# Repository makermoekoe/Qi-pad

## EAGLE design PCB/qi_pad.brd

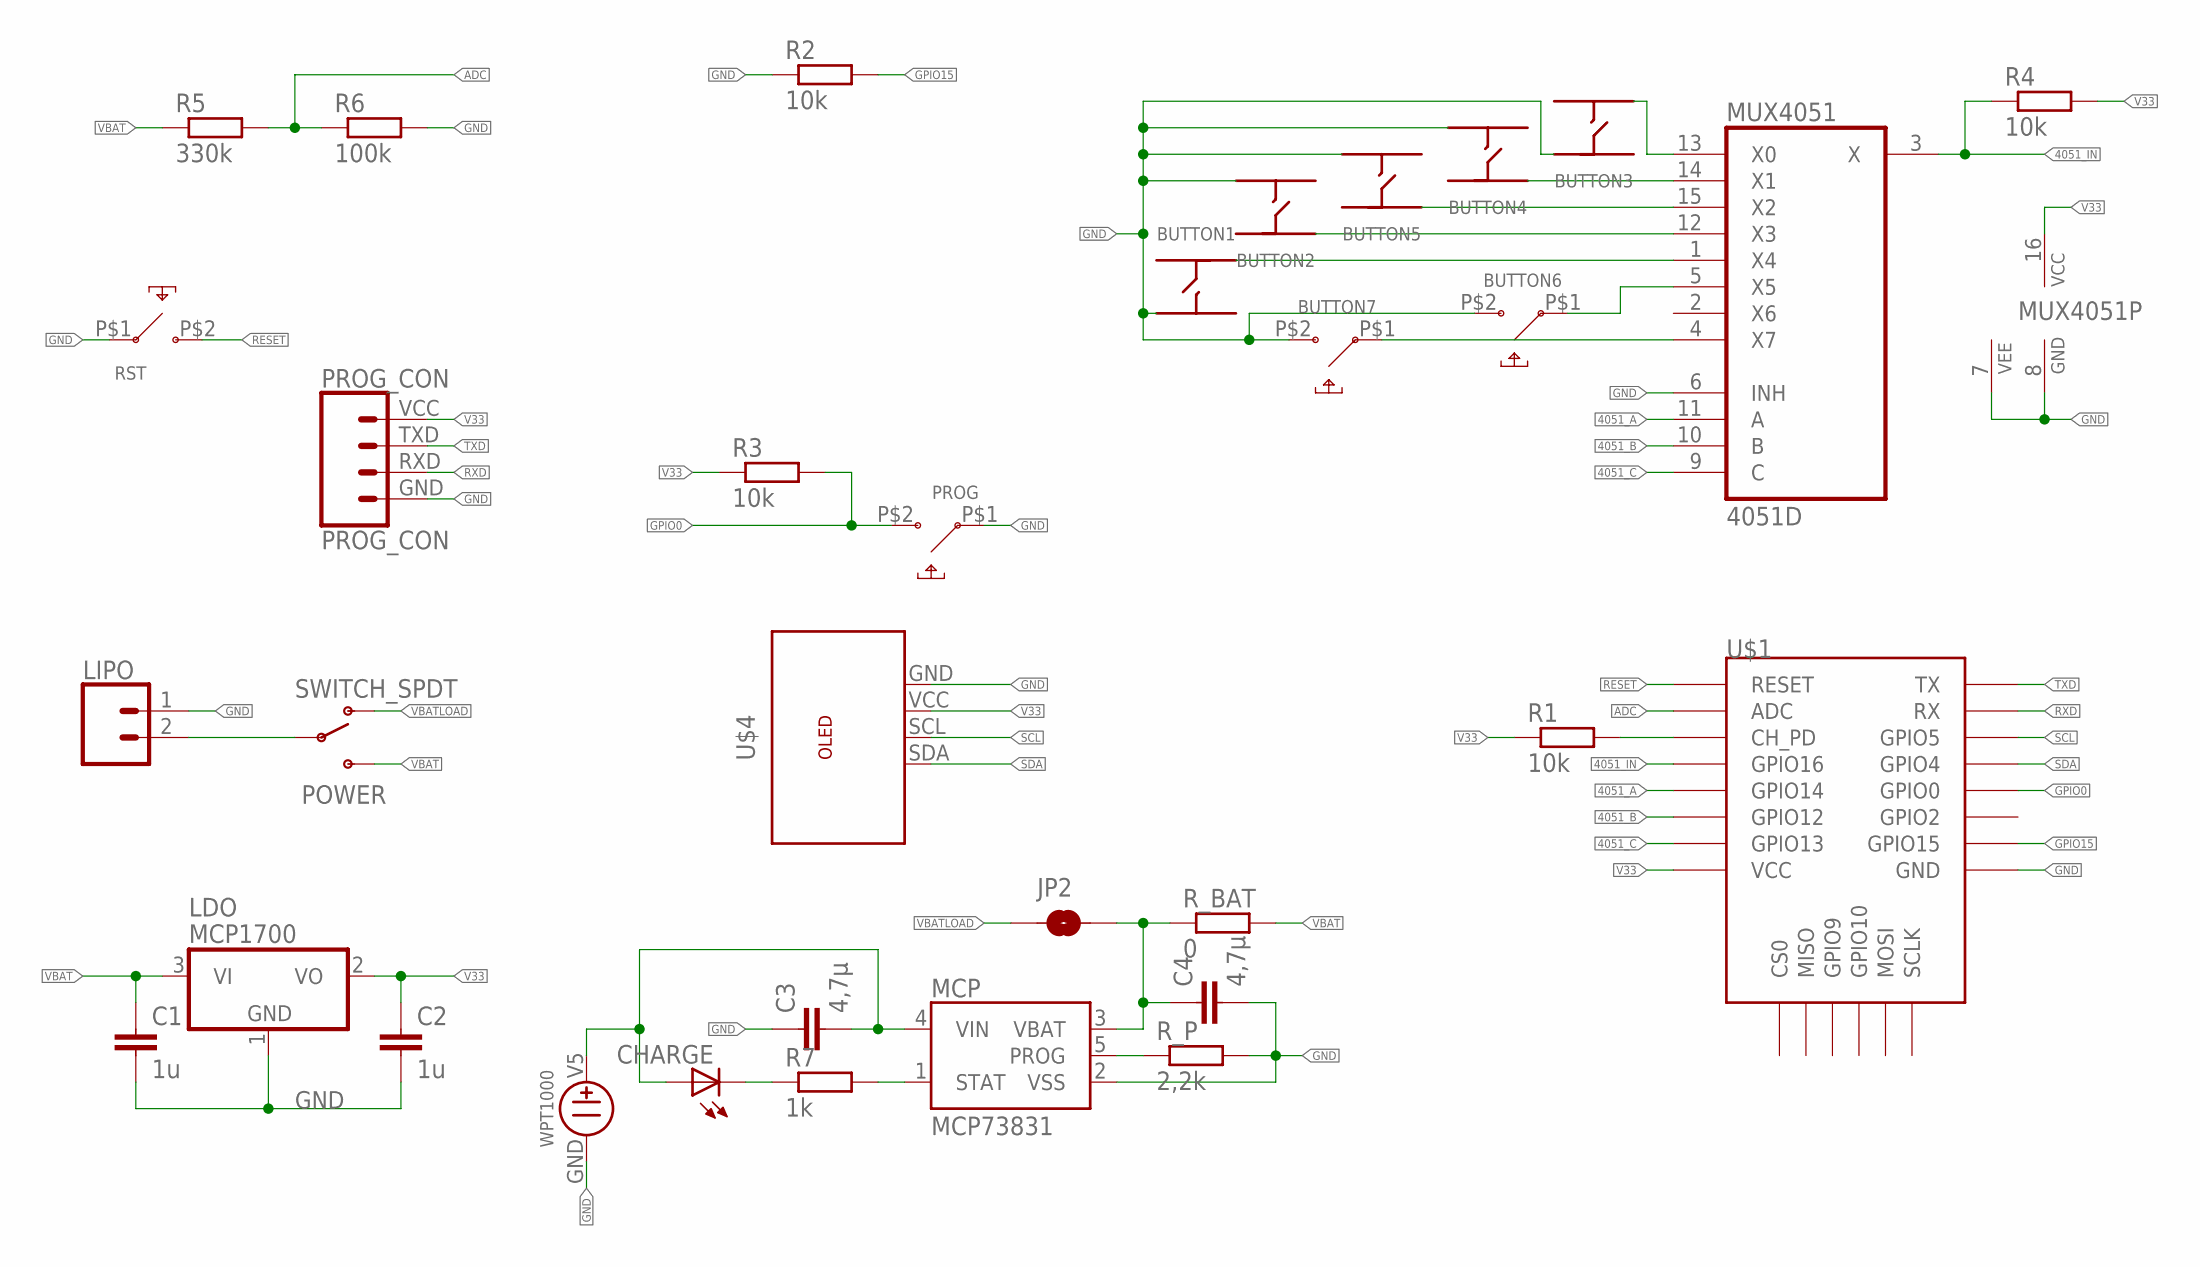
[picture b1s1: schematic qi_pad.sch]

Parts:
BUTTON1, BUTTON2, BUTTON3, BUTTON4, BUTTON5: 6X6BUTTON
BUTTON6, BUTTON7: 3X4_SMD_BUTTON; 3X4BUTTON
C1, C2: 1u; C1206
C3, C4: 4,7µ; C1206
CHARGE: LEDCHIPLED_1206; CHIPLED_1206
JP2: JUMPER-SMT_2_NO_NO-SILK; SMT-JUMPER_2_NO_NO-SILK
LDO: MCP1700; SOT23
LIPO: CONN_02-JST-2MM-SMT; JST-2-SMD
MCP: MCP73831; SOT23-5
MUX4051: 4051D; SO16
POWER: SWITCH_SPDT; KPS-1290
PROG: 3X6X3,5BUTTON90
PROG_CON: PROG_CON
R1, R2, R3, R4: 10k; R0603
R5: 330k; R0603
R6: 100k; R0603
R7: 1k; R0603
RST: 3X6X3,5BUTTON90
R_BAT: 0; R1206
R_P: 2,2k; R0603
U$1: ESP8266-12F-SMD; ESP8266-12F
U$4: OLED128X64; OLED_128X64
WPM1000: WPT1000

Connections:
4051_A: MUX4051.11 (A), U$1.GPIO14
4051_B: MUX4051.10 (B), U$1.GPIO12
4051_C: MUX4051.9 (C), U$1.GPIO13
4051_IN: MUX4051.3 (X), R4.1, U$1.GPIO16
ADC: R5.2, R6.1, U$1.ADC
GND: BUTTON1.P1 (A1), BUTTON2.P2 (A2), BUTTON3.P4 (U2), BUTTON4.P2 (A2), BUTTON5.P2 (A2), BUTTON6.P$2 (P2), BUTTON7.P$2 (P2), C1.2, C2.2, C3.1, C4.2, LDO.1 (GND), LIPO.1 (2), MCP.2 (VSS), MUX4051.6 (INH), MUX4051.7 (VEE), MUX4051.8 (GND), PROG.P$1 (P1), PROG_CON.GND (1), R2.1, R6.2, RST.P$1 (P1), R_P.2, U$1.GND, U$4.GND, WPM1000.GND
GPIO0: PROG.P$2 (P2), R3.2, U$1.GPIO0
GPIO15: R2.2, U$1.GPIO15
unnamed: BUTTON3.P1 (A1), MUX4051.13 (X0)
unnamed: LIPO.2 (1), POWER.P
unnamed: BUTTON6.P$1 (P1), MUX4051.5 (X5)
unnamed: MCP.1 (STAT), R7.2
unnamed: R1.2, U$1.EN (CH_PD)
unnamed: BUTTON7.P$1 (P1), MUX4051.4 (X7)
unnamed: BUTTON1.P4 (U2), MUX4051.1 (X4)
unnamed: MCP.5 (PROG), R_P.1
unnamed: BUTTON2.P3 (U1), MUX4051.12 (X3)
unnamed: CHARGE.C, R7.1
unnamed: BUTTON5.P3 (U1), MUX4051.15 (X2)
unnamed: BUTTON4.P3 (U1), MUX4051.14 (X1)
unnamed: C4.1, JP2.2, MCP.3 (VBAT), R_BAT.1
RESET: RST.P$2 (P2), U$1.RESET
RXD: PROG_CON.RXD (2), U$1.RXD (RX)
SCL: U$1.GPIO5, U$4.SCL
SDA: U$1.GPIO4, U$4.SDA
TXD: PROG_CON.TXD (3), U$1.TXD (TX)
V5: C3.2, CHARGE.A, MCP.4 (VIN), WPM1000.V5
V33: C2.1, LDO.2 (VO), MUX4051.16 (VCC), PROG_CON.VCC (4), R1.1, R3.1, R4.2, U$1.VCC, U$4.VCC
VBAT: C1.1, LDO.3 (VI), POWER.S, R5.1, R_BAT.2
VBATLOAD: JP2.1, POWER.O

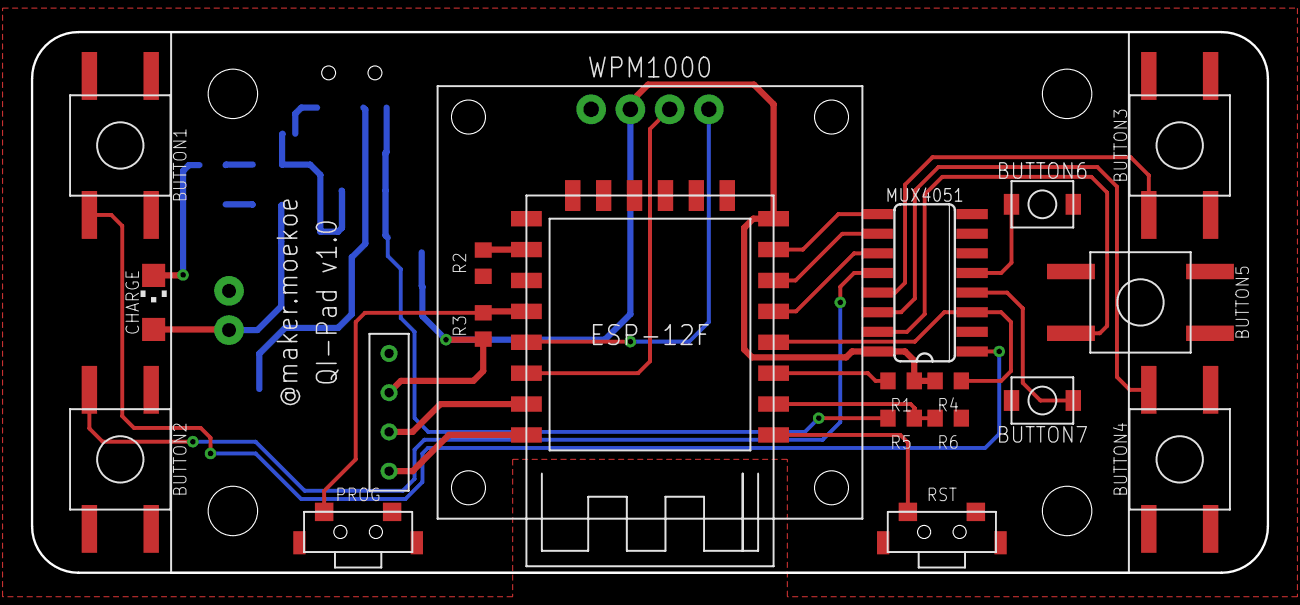
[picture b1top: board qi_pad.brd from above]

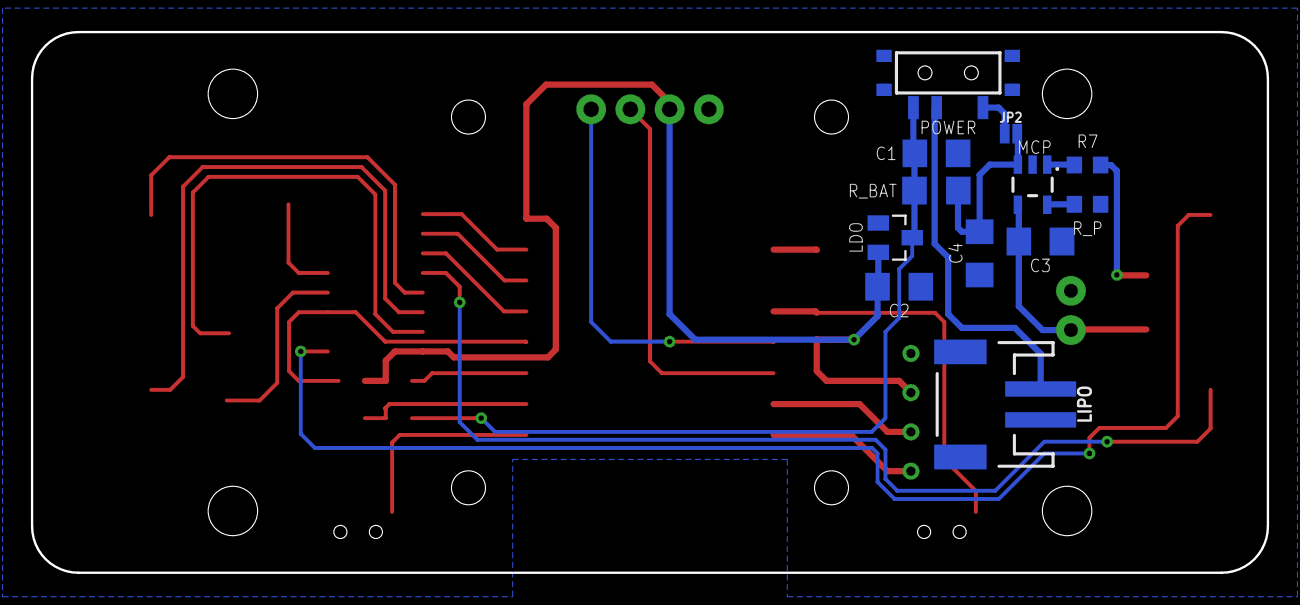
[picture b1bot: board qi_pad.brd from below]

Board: 2 copper layers, 80.0 x 35.0 mm, 33 parts (12 on the bottom side), 30 nets.

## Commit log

2019-02-10 basic idea
2019-02-10 added description and pictures
2019-05-22 added some videos
2019-05-22 added 3d printing case
2019-05-22 added videos

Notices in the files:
parts and their libraries:
SparkFun-Retired: Licensing: Creative Commons ShareAlike 4.0 International - https://creativecommons.org/licenses/by-sa/4.0
